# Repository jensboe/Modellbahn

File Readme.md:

# System architecture
The `adapter board A` is connected to a nucleo 64 board.
The `adapter board A` provides a 
```mermaid
block-beta

columns 1
block:selfmade
    block:base
        columns 1
        nucleo
        adapter["adapter board A"]
    end
    space
    expansion_1["expansion board A 1"]
    space
    expansion_n["expansion board A n"]
    space
    expansion_b["expansion board B"]
    adapter     <--> expansion_1
    expansion_1   ----> expansion_n
    expansion_n  ----> expansion_b
    style expansion_b stroke:#333,stroke-dasharray: 5 5;
end
space
block:extern
    power_supply
    track_1
    switch_1_a
    switch_1_b
    track_x
    switch_y_a
    switch_y_b
end
power_supply --> adapter
expansion_1 --> track_1
expansion_1 --> switch_1_a
expansion_1 --> switch_1_b

expansion_n --> track_x
expansion_n --> switch_y_a
expansion_n --> switch_y_b
```
## Connection between expansion boards
Required Wires:
1. Drive Ground
2. Drive voltage
3. Switch voltage
4. Vcc (3V3 or 5V?)
5. D_Ground
6. MOSI
7. MISO
8. CLK

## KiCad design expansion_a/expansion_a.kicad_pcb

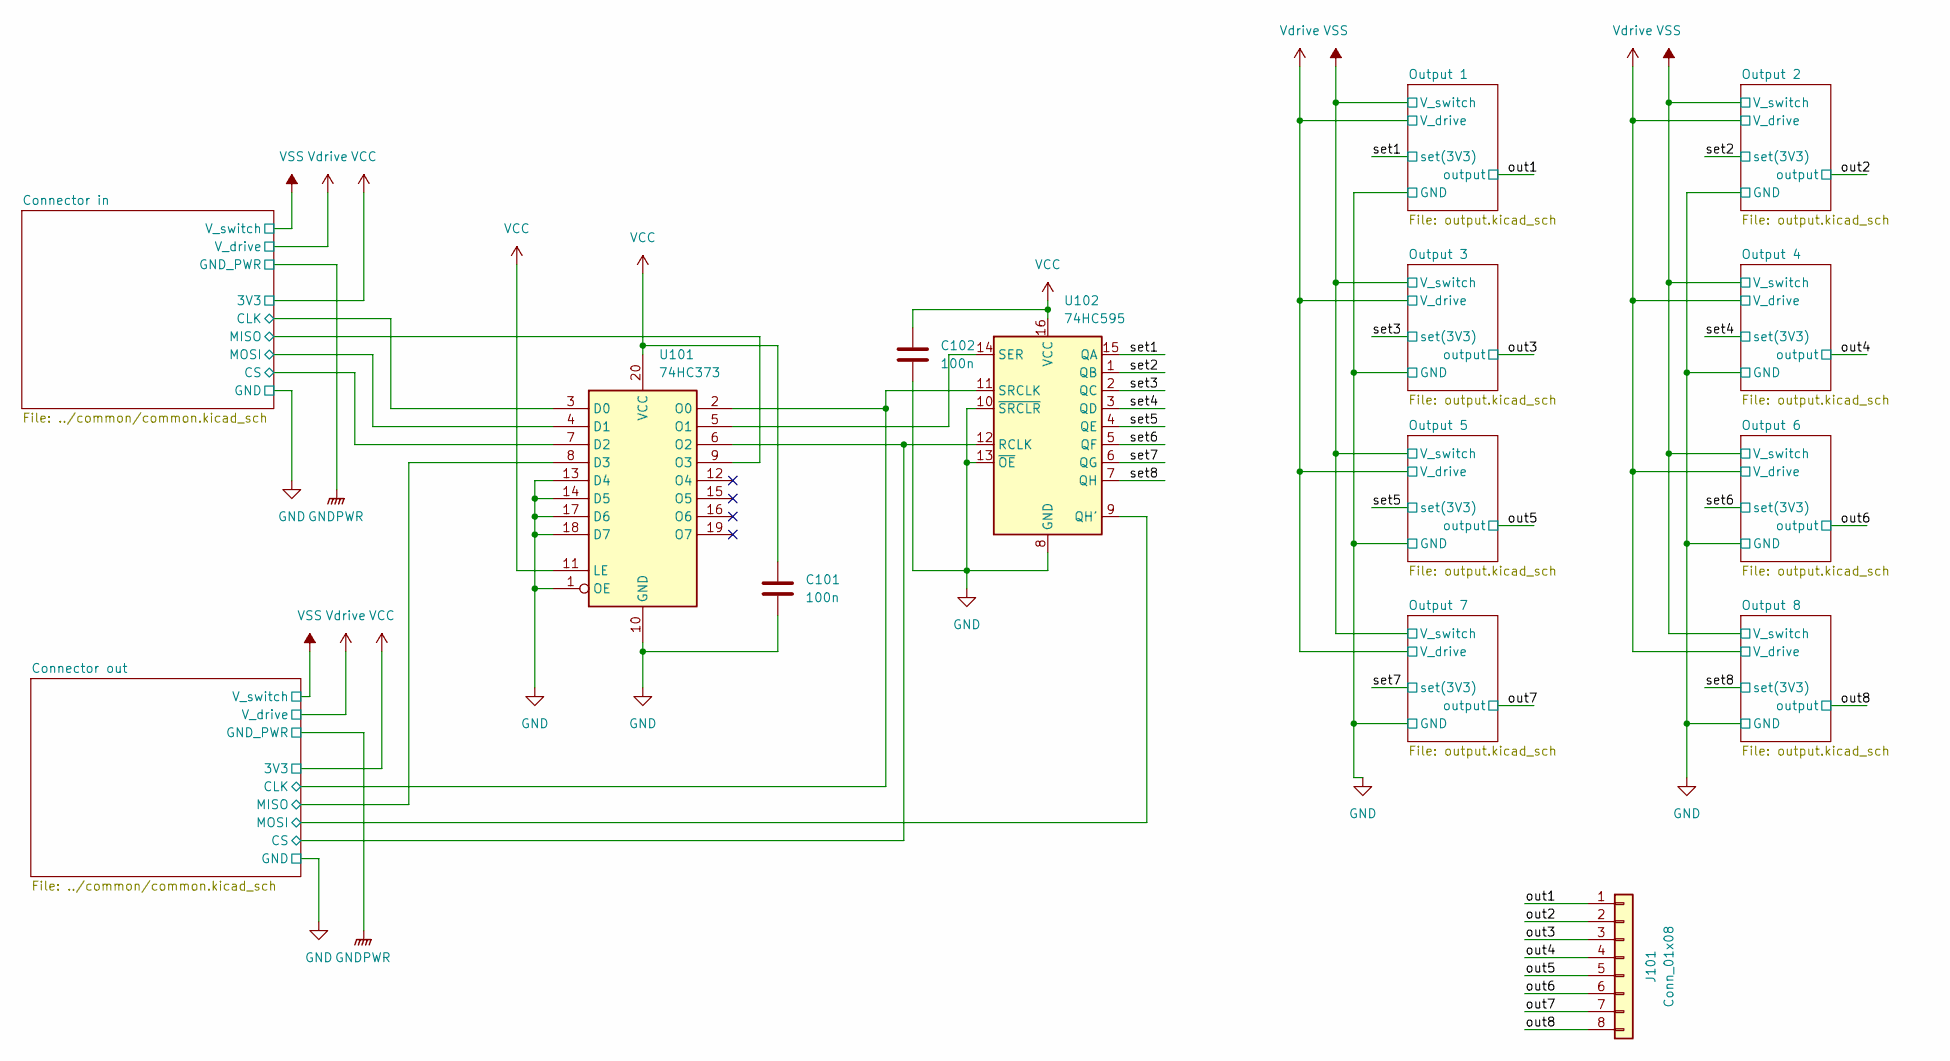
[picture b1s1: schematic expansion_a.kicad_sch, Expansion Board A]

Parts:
C101, C102: 100n; C_0805_2012Metric; LCSC C28233
J101: Conn_01x08; TerminalBlock_4Ucon_1x08_P3.50mm_Vertical; LCSC C976562
U101: 74HC373; SO-20_5.3x12.6mm_P1.27mm; LCSC C22374060
U102: 74HC595; SOIC-16W_5.3x10.2mm_P1.27mm; LCSC C5947

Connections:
/Connector in/CLK: U101.3 (D0); also elsewhere on the board
/Connector in/CS: U101.7 (D2); also elsewhere on the board
/Connector in/MISO: U101.9 (O3); also elsewhere on the board
/Connector in/MOSI: U101.4 (D1); also elsewhere on the board
/Connector out/CLK: U101.2 (O0), U102.11 (SRCLK); also elsewhere on the board
/Connector out/CS: U101.6 (O2), U102.12 (RCLK); also elsewhere on the board
/Connector out/MISO: U101.8 (D3); also elsewhere on the board
/Connector out/MOSI: U102.9 (QH'); also elsewhere on the board
/out1: J101.1; also elsewhere on the board
/out2: J101.2; also elsewhere on the board
/out3: J101.3; also elsewhere on the board
/out4: J101.4; also elsewhere on the board
/out5: J101.5; also elsewhere on the board
/out6: J101.6; also elsewhere on the board
/out7: J101.7; also elsewhere on the board
/out8: J101.8; also elsewhere on the board
/set1: U102.15 (QA); also elsewhere on the board
/set2: U102.1 (QB); also elsewhere on the board
/set3: U102.2 (QC); also elsewhere on the board
/set4: U102.3 (QD); also elsewhere on the board
/set5: U102.4 (QE); also elsewhere on the board
/set6: U102.5 (QF); also elsewhere on the board
/set7: U102.6 (QG); also elsewhere on the board
/set8: U102.7 (QH); also elsewhere on the board
GND: C101.2, C102.2, U101.1 (OE), U101.10 (GND), U101.13 (D4), U101.14 (D5), U101.17 (D6), U101.18 (D7), U102.8 (GND), U102.10 (~SRCLR), U102.13 (~OE); also elsewhere on the board
unnamed: U101.5 (O1), U102.14 (SER)
VCC: C101.1, C102.1, U101.11 (LE), U101.20 (VCC), U102.16 (VCC); also elsewhere on the board

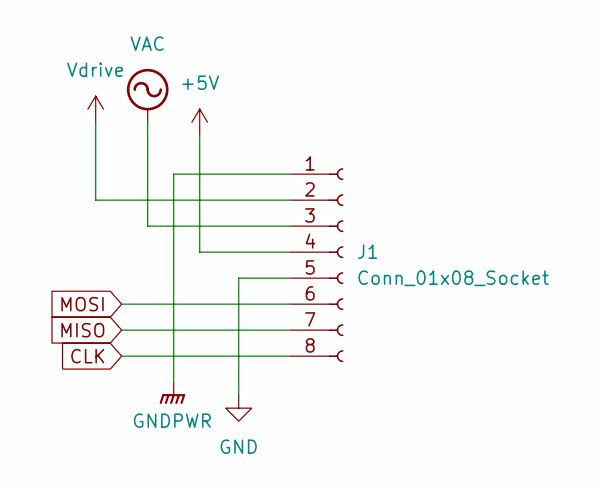
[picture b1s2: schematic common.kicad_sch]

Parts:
J1: Conn_01x08_Socket; TerminalBlock_4Ucon_1x08_P3.50mm_Vertical; LCSC C976562

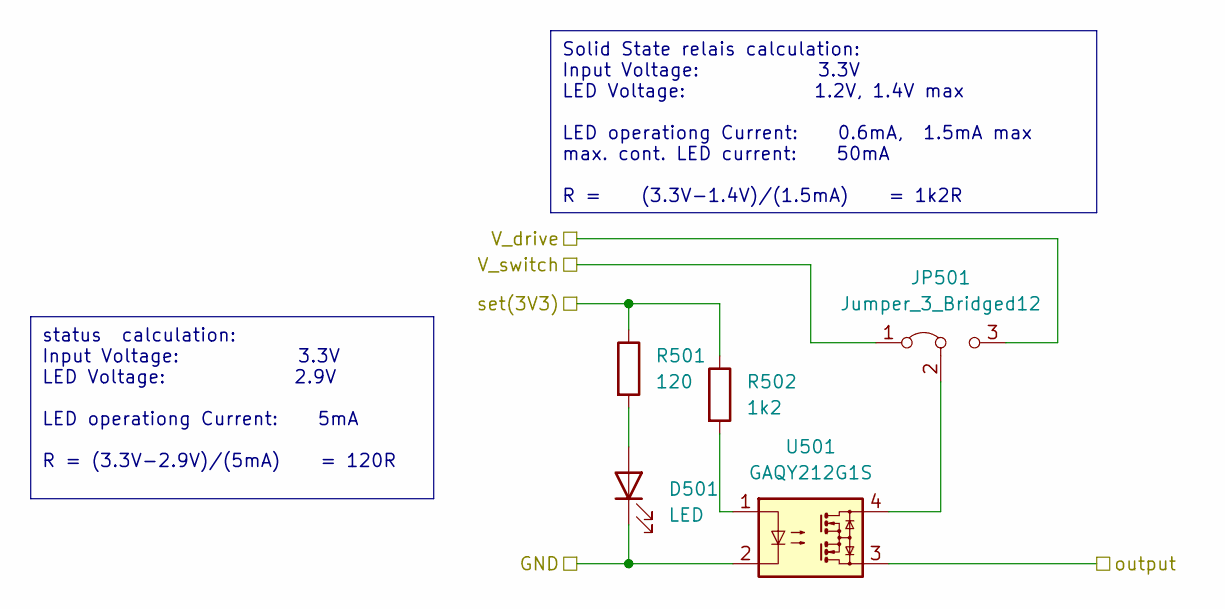
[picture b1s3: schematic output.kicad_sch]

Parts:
D501: LED; CP_EIA-3528-12_Kemet-T; LCSC C2290
JP501: Jumper_3_Bridged12; PinHeader_1x03_P2.54mm_Vertical; LCSC C124376
R501: 120; R_0805_2012Metric; LCSC C17437
R502: 1k2; R_0805_2012Metric; LCSC C17379
U501: GAQY212G1S; SO-4_4.4x3.9mm_P2.54mm; LCSC C7435108

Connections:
/out3: U501.3; also elsewhere on the board
/set3: R501.1, R502.1; also elsewhere on the board
GND: D501.1 (K), U501.2; also elsewhere on the board
unnamed: D501.2 (A), R501.2
unnamed: JP501.2 (C), U501.4
unnamed: R502.2, U501.1
VSS: JP501.1 (A); also elsewhere on the board
Vdrive: JP501.3 (B); also elsewhere on the board

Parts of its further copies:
D301, D401, D601, D701, D801, D901, D1001: LED; CP_EIA-3528-12_Kemet-T; LCSC C2290
JP301, JP401, JP601, JP701, JP801, JP901, JP1001: Jumper_3_Bridged12; PinHeader_1x03_P2.54mm_Vertical; LCSC C124376
R301, R401, R601, R701, R801, R901, R1001: 120; R_0805_2012Metric; LCSC C17437
R302, R402, R602, R702, R802, R902, R1002: 1k2; R_0805_2012Metric; LCSC C17379
U301, U401, U601, U701, U801, U901, U1001: GAQY212G1S; SO-4_4.4x3.9mm_P2.54mm; LCSC C7435108

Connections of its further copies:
/out1: U301.3; also elsewhere on the board
/out2: U401.3; also elsewhere on the board
/out4: U601.3; also elsewhere on the board
/out5: U701.3; also elsewhere on the board
/out6: U801.3; also elsewhere on the board
/out7: U901.3; also elsewhere on the board
/out8: U1001.3; also elsewhere on the board
/set1: R301.1, R302.1; also elsewhere on the board
/set2: R401.1, R402.1; also elsewhere on the board
/set4: R601.1, R602.1; also elsewhere on the board
/set5: R701.1, R702.1; also elsewhere on the board
/set6: R801.1, R802.1; also elsewhere on the board
/set7: R901.1, R902.1; also elsewhere on the board
/set8: R1001.1, R1002.1; also elsewhere on the board
GND: D301.1 (K), D401.1 (K), D601.1 (K), D701.1 (K), D801.1 (K), D901.1 (K), D1001.1 (K), U301.2, U401.2, U601.2, U701.2, U801.2, U901.2, U1001.2; also elsewhere on the board
unnamed: D301.2 (A), R301.2
unnamed: D401.2 (A), R401.2
unnamed: D601.2 (A), R601.2
unnamed: D701.2 (A), R701.2
unnamed: D801.2 (A), R801.2
unnamed: D901.2 (A), R901.2
unnamed: D1001.2 (A), R1001.2
unnamed: JP301.2 (C), U301.4
unnamed: JP401.2 (C), U401.4
unnamed: JP601.2 (C), U601.4
unnamed: JP701.2 (C), U701.4
unnamed: JP801.2 (C), U801.4
unnamed: JP901.2 (C), U901.4
unnamed: JP1001.2 (C), U1001.4
unnamed: R302.2, U301.1
unnamed: R402.2, U401.1
unnamed: R602.2, U601.1
unnamed: R702.2, U701.1
unnamed: R802.2, U801.1
unnamed: R902.2, U901.1
unnamed: R1002.2, U1001.1
VSS: JP301.1 (A), JP401.1 (A), JP601.1 (A), JP701.1 (A), JP801.1 (A), JP901.1 (A), JP1001.1 (A); also elsewhere on the board
Vdrive: JP301.3 (B), JP401.3 (B), JP601.3 (B), JP701.3 (B), JP801.3 (B), JP901.3 (B), JP1001.3 (B); also elsewhere on the board

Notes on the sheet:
Solid State relais calculation: Input Voltage: 3.3V LED Voltage: 1.2V, 1.4V max LED operationg Current: 0.6mA, 1.5mA max max. cont. LED current: 50mA R = (3.3V-1.4V)/(1.5mA) = 1k2R
status calculation: Input Voltage: 3.3V LED Voltage: 2.9V LED operationg Current: 5mA R = (3.3V-2.9V)/(5mA) = 120R

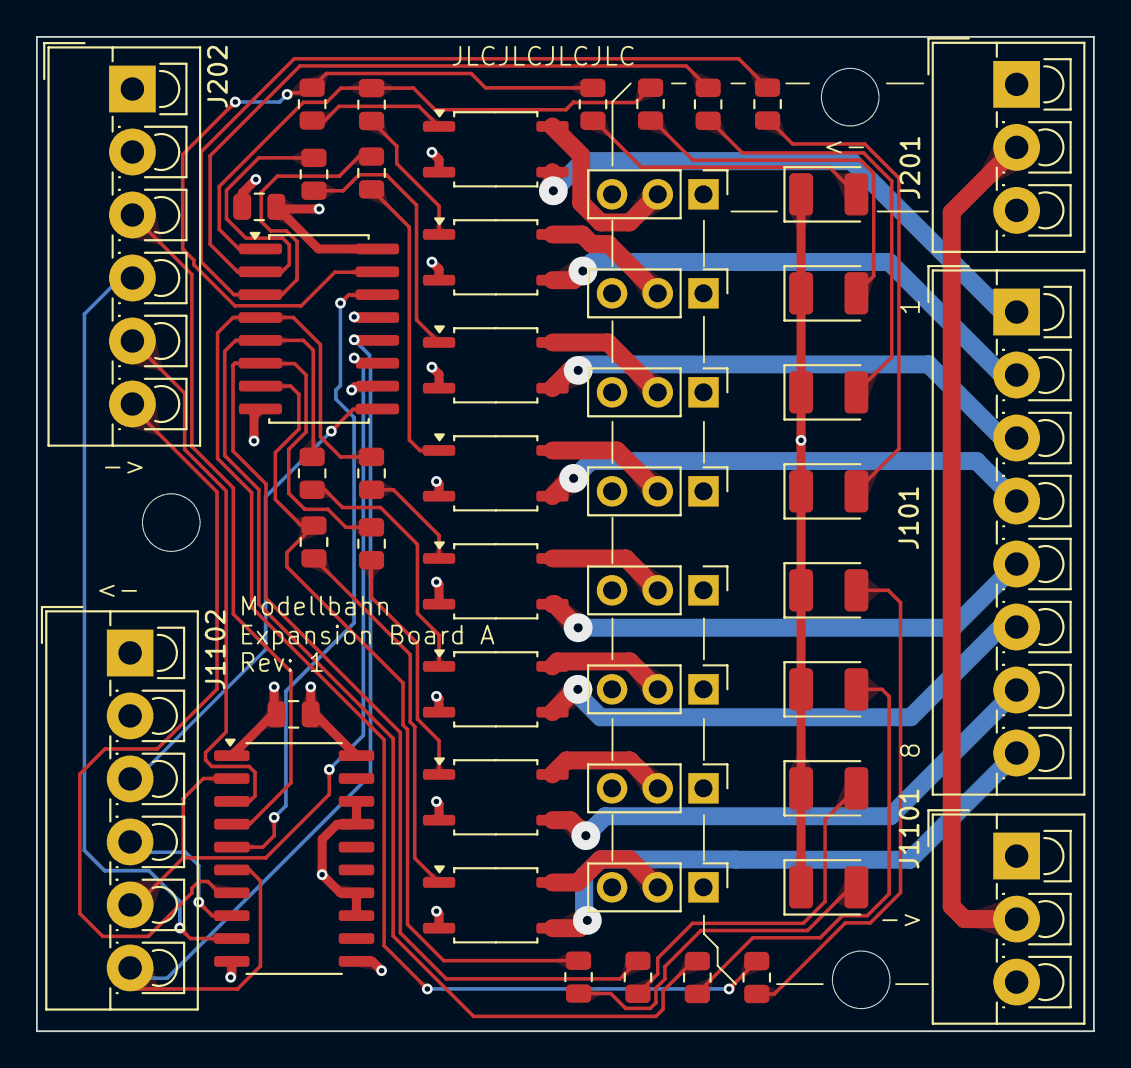
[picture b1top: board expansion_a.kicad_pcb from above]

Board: 4 copper layers, 58.7 x 55.2 mm, 52 parts (0 on the bottom side), 54 nets.

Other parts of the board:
J201, J1101: Conn_01x03; TerminalBlock_4Ucon_1x03_P3.50mm_Vertical
J202, J1102: Conn_01x06; TerminalBlock_4Ucon_1x06_P3.50mm_Vertical
REF1, REF2, REF3: MountingHole_3.2mm_M3

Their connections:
/Connector in/CLK: J202.5; also elsewhere on the board
/Connector in/CS: J202.6; also elsewhere on the board
/Connector in/MISO: J202.4; also elsewhere on the board
/Connector in/MOSI: J202.3; also elsewhere on the board
/Connector out/CLK: J1102.5; also elsewhere on the board
/Connector out/CS: J1102.6; also elsewhere on the board
/Connector out/MISO: J1102.4; also elsewhere on the board
/Connector out/MOSI: J1102.3; also elsewhere on the board
GND: J202.2, J1102.2; also elsewhere on the board
GNDPWR: J201.2, J1101.2
VCC: J202.1, J1102.1; also elsewhere on the board
VSS: J201.3, J1101.3; also elsewhere on the board
Vdrive: J201.1, J1101.1; also elsewhere on the board

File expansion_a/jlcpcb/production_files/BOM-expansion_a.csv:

Comment,Designator,Footprint,LCSC,Quantity
Jumper_3_Bridged12,"JP1001,JP301,JP401,JP501,JP601,JP701,JP801,JP901",PinHeader_1x03_P2.54mm_Vertical,C124376,8
1k2,"R1002,R302,R402,R502,R602,R702,R802,R902",R_0805_2012Metric,C17379,8
120,"R1001,R301,R401,R501,R601,R701,R801,R901",R_0805_2012Metric,C17437,8
74HC373,U101,SO-20_5.3x12.6mm_P1.27mm,C22374060,1
100n,"C101,C102",C_0805_2012Metric,C28233,2
LED,"D1001,D301,D401,D501,D601,D701,D801,D901",CP_EIA-3528-12_Kemet-T,C5246350,8
74HC595,U102,SOIC-16W_5.3x10.2mm_P1.27mm,C5947,1
GAQY212G1S,"U1001,U301,U401,U501,U601,U701,U801,U901",SO-4_4.4x3.9mm_P2.54mm,C7435108,8
Conn_01x03,"J1101,J201",TerminalBlock_4Ucon_1x03_P3.50mm_Vertical,C976557,2
Conn_01x06,"J1102,J202",TerminalBlock_4Ucon_1x06_P3.50mm_Vertical,C976560,2
Conn_01x08,J101,TerminalBlock_4Ucon_1x08_P3.50mm_Vertical,C976562,1

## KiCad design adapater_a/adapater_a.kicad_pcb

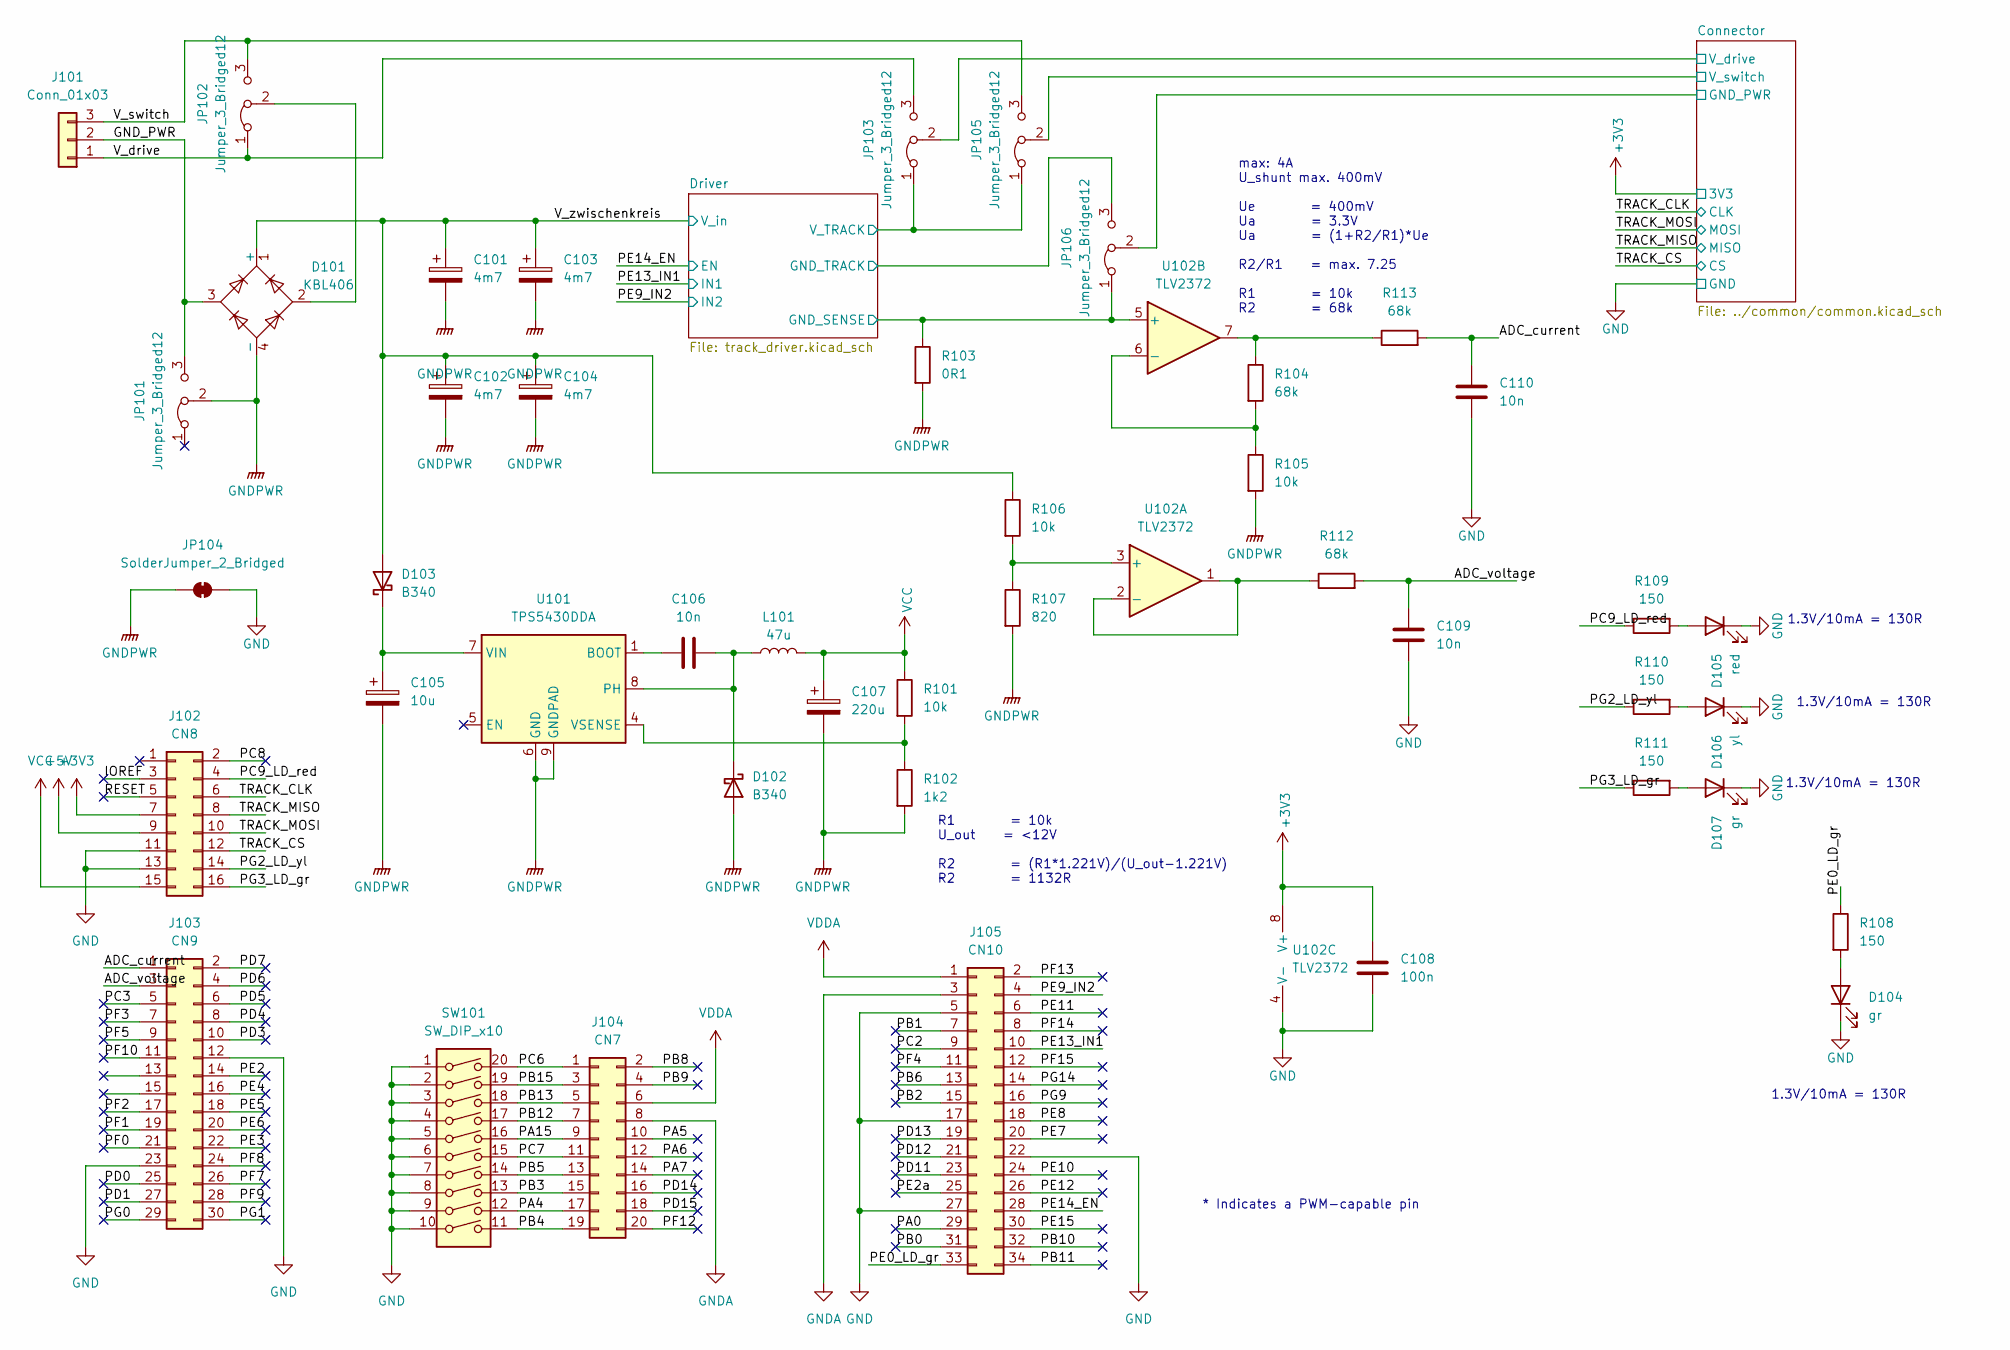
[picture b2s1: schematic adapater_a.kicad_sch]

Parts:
C101, C102, C103, C104: 4m7; CP_Radial_D18.0mm_P7.50mm; LCSC C92163
C105: 10u; CP_Elec_6.3x5.4; LCSC C29199
C106, C109, C110: 10n; C_0805_2012Metric; LCSC C1710
C107: 220u; C_Elec_10x10.2; LCSC C3358
C108: 100n; C_0805_2012Metric; LCSC C28233
D101: KBL406; Diode_Bridge_Vishay_KBL; LCSC C3078
D102, D103: B340; D_SMA; LCSC C64982
D104, D107: gr; LED_0805_2012Metric; LCSC C2297
D105: red; LED_0805_2012Metric; LCSC C84256
D106: yl; LED_0805_2012Metric; LCSC C2296
J101: Conn_01x03; TerminalBlock_4Ucon_1x03_P3.50mm_Vertical; LCSC C976557
J102: CN8; PinHeader_2x08_P2.54mm_Vertical; LCSC C68234
J103: CN9; PinHeader_2x15_P2.54mm_Vertical; LCSC C56496
J104: CN7; PinHeader_2x10_P2.54mm_Vertical; LCSC C5116480
J105: CN10; PinHeader_2x17_P2.54mm_Vertical; LCSC C2685134
JP101, JP102, JP103, JP105, JP106: Jumper_3_Bridged12; PinHeader_1x03_P2.54mm_Vertical; LCSC C124376
JP104: SolderJumper_2_Bridged; SolderJumper-2_P1.3mm_Bridged_RoundedPad1.0x1.5mm
L101: 47u; L_Ferrocore_DLG-0504; LCSC C9889
R101, R105, R106: 10k; R_0805_2012Metric; LCSC C17414
R102: 1k2; R_0805_2012Metric; LCSC C17379
R103: 0R1; R_1206_3216Metric; LCSC C25334
R104, R112, R113: 68k; R_0805_2012Metric; LCSC C17801
R107: 820; R_0805_2012Metric; LCSC C23253
R108, R109, R110, R111: 150; R_0805_2012Metric; LCSC C17471
SW101: SW_DIP_x10; SW_DIP_SPSTx10_Slide_KingTek_DSHP10TS_W7.62mm_P1.27mm; LCSC C314500
U101: TPS5430DDA; TI_SO-PowerPAD-8_ThermalVias; LCSC C9864
U102: TLV2372; SOIC-8_3.9x4.9mm_P1.27mm; LCSC C27204

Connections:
+3V3: C108.1, J102.7, U102.8 (V+); also elsewhere on the board
+5V: J102.9
/ADC_current: C110.2, J103.1, R113.2
/ADC_voltage: C109.2, J103.3, R112.2
/Connector/GND_PWR: JP106.2 (C); also elsewhere on the board
/Connector/V_drive: JP103.2 (C); also elsewhere on the board
/Connector/V_switch: JP105.2 (C); also elsewhere on the board
/Driver/GND_SENSE: JP106.1 (A), R103.1, U102.5 (+); also elsewhere on the board
/Driver/GND_TRACK: JP106.3 (B); also elsewhere on the board
/Driver/V_TRACK: JP103.1 (A), JP105.1 (A); also elsewhere on the board
/GND_PWR: D101.3, J101.2, JP101.3 (B)
/IOREF: J102.3
/PA0: J105.29
/PA4: J104.17, SW101.12
/PA5: J104.10
/PA6: J104.12
/PA7: J104.14
/PA15: J104.9, SW101.16
/PB0: J105.31
/PB1: J105.7
/PB2: J105.15
/PB3: J104.15, SW101.13
/PB4: J104.19, SW101.11
/PB5: J104.13, SW101.14
/PB6: J105.13
/PB8: J104.2
/PB9: J104.4
/PB10: J105.32
/PB11: J105.34
/PB12: J104.7, SW101.17
/PB13: J104.5, SW101.18
/PB15: J104.3, SW101.19
/PC2: J105.9
/PC3: J103.5
/PC6: J104.1, SW101.20
/PC7: J104.11, SW101.15
/PC8: J102.2
/PC9_LD_red: J102.4, R109.1
/PD0: J103.25
/PD1: J103.27
/PD3: J103.10
/PD4: J103.8
/PD5: J103.6
/PD6: J103.4
/PD7: J103.2
/PD11: J105.23
/PD12: J105.21
/PD13: J105.19
/PD14: J104.16
/PD15: J104.18
/PE0_LD_gr: J105.33, R108.1
/PE2: J103.14
/PE2a: J105.25
/PE3: J103.22
/PE4: J103.16
/PE5: J103.18
/PE6: J103.20
/PE7: J105.20
/PE8: J105.18
/PE9_IN2: J105.4; also elsewhere on the board
/PE10: J105.24
/PE11: J105.6
/PE12: J105.26
/PE13_IN1: J105.10; also elsewhere on the board
/PE14_EN: J105.28; also elsewhere on the board
/PE15: J105.30
/PF0: J103.21
/PF1: J103.19
/PF2: J103.17
/PF3: J103.7
/PF4: J105.11
/PF5: J103.9
/PF7: J103.26
/PF8: J103.24
/PF9: J103.28
/PF10: J103.11
/PF12: J104.20
/PF13: J105.2
/PF14: J105.8
/PF15: J105.12
/PG0: J103.29
/PG1: J103.30
/PG2_LD_yl: J102.14, R110.1
/PG3_LD_gr: J102.16, R111.1
/PG9: J105.16
/PG14: J105.14
/RESET: J102.5
/TRACK_CLK: J102.6; also elsewhere on the board
/TRACK_CS: J102.12; also elsewhere on the board
/TRACK_MISO: J102.8; also elsewhere on the board
/TRACK_MOSI: J102.10; also elsewhere on the board
/V_drive: J101.1, JP102.1 (A), JP103.3 (B)
/V_switch: J101.3, JP102.3 (B), JP105.3 (B)
/V_zwischenkreis: C101.1, C102.1, C103.1, C104.1, D101.1 (+), D103.2 (A), R106.1; also elsewhere on the board
GND: C108.2, C109.1, C110.1, D104.1 (K), D105.1 (K), D106.1 (K), D107.1 (K), J102.11, J102.13, J103.12, J103.23, J105.5, J105.17, J105.22, J105.27, JP104.2 (B), SW101.1, SW101.2, SW101.3, SW101.4, SW101.5, SW101.6, SW101.7, SW101.8, SW101.9, SW101.10, U102.4 (V-); also elsewhere on the board
GNDA: J104.8, J105.3
GNDPWR: C101.2, C102.2, C103.2, C104.2, C105.2, C107.2, D101.4 (-), D102.2 (A), JP101.2 (C), JP104.1 (A), R102.2, R103.2, R105.2, R107.2, U101.6 (GND), U101.9 (GNDPAD); also elsewhere on the board
unnamed: C106.2, D102.1 (K), L101.1, U101.8 (PH)
unnamed: C105.1, D103.1 (K), U101.7 (VIN)
unnamed: D104.2 (A), R108.2
unnamed: D105.2 (A), R109.2
unnamed: D106.2 (A), R110.2
unnamed: D107.2 (A), R111.2
unnamed: D101.2, JP102.2 (C)
unnamed: R104.1, R113.1, U102.7
unnamed: C106.1, U101.1 (BOOT)
unnamed: R101.2, R102.1, U101.4 (VSENSE)
unnamed: R106.2, R107.1, U102.3 (+)
unnamed: R112.1, U102.1, U102.2 (-)
unnamed: R104.2, R105.1, U102.6 (-)
VCC: C107.1, J102.15, L101.2, R101.1
VDDA: J104.6, J105.1

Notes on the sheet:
1.3V/10mA = 130R
R1 = 10k U_out = <12V R2 = (R1*1.221V)/(U_out-1.221V) R2 = 1132R
max: 4A U_shunt max. 400mV Ue = 400mV Ua = 3.3V Ua = (1+R2/R1)*Ue R2/R1 = max. 7.25 R1 = 10k R2 = 68k
* Indicates a PWM-capable pin

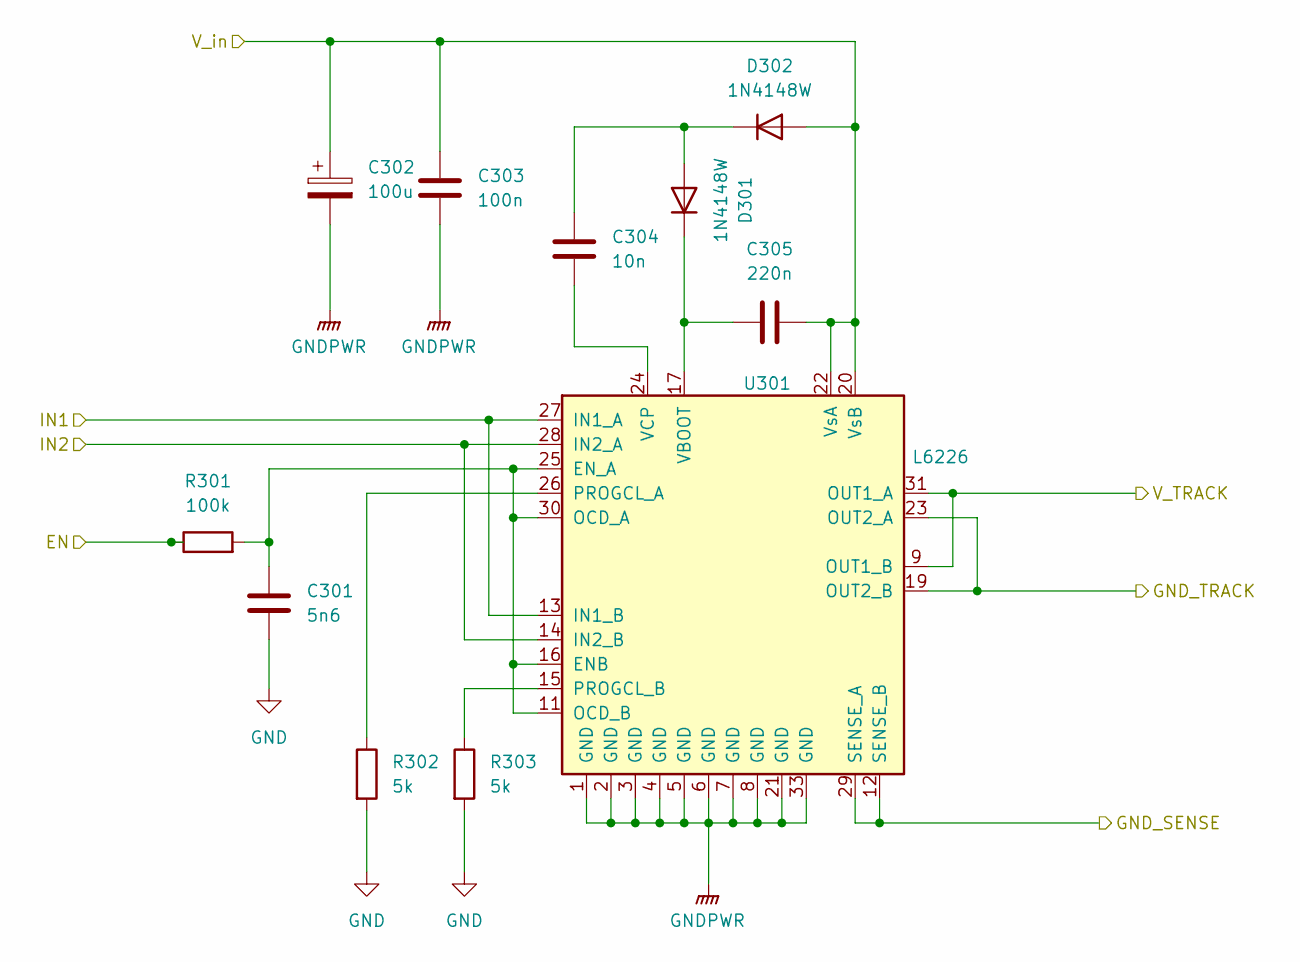
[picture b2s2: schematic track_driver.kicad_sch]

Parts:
C301: 5n6; C_0805_2012Metric; LCSC C56078
C302: 100u; CP_Elec_6.3x5.4; LCSC C37308
C303: 100n; C_0805_2012Metric; LCSC C28233
C304: 10n; C_0805_2012Metric; LCSC C1710
C305: 220n; C_0805_2012Metric; LCSC C1710
D301, D302: 1N4148W; D_SOD-123; LCSC C81598
R301: 100k; R_0805_2012Metric; LCSC C149504
R302, R303: 5k; R_0805_2012Metric; LCSC C17379
U301: L6226; UFQFPN-32-1EP_5x5mm_P0.5mm_EP3.5x3.5mm; LCSC C95357

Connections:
/Driver/GND_SENSE: U301.12 (SENSE_B), U301.29 (SENSE_A); also elsewhere on the board
/Driver/GND_TRACK: U301.19 (OUT2_B), U301.23 (OUT2_A); also elsewhere on the board
/Driver/V_TRACK: U301.9 (OUT1_B), U301.31 (OUT1_A); also elsewhere on the board
/PE9_IN2: U301.14 (IN2_B), U301.28 (IN2_A); also elsewhere on the board
/PE13_IN1: U301.13 (IN1_B), U301.27 (IN1_A); also elsewhere on the board
/PE14_EN: R301.1; also elsewhere on the board
/V_zwischenkreis: C302.1, C303.1, C305.2, D302.2 (A), U301.20 (VsB), U301.22 (VsA); also elsewhere on the board
GND: C301.2, R302.2, R303.2; also elsewhere on the board
GNDPWR: C302.2, C303.2, U301.1 (GND), U301.2 (GND), U301.3 (GND), U301.4 (GND), U301.5 (GND), U301.6 (GND), U301.7 (GND), U301.8 (GND), U301.21 (GND), U301.33 (GND); also elsewhere on the board
unnamed: C304.1, D301.2 (A), D302.1 (K)
unnamed: C305.1, D301.1 (K), U301.17 (VBOOT)
unnamed: C301.1, R301.2, U301.11 (OCD_B), U301.16 (ENB), U301.25 (EN_A), U301.30 (OCD_A)
unnamed: R302.1, U301.26 (PROGCL_A)
unnamed: R303.1, U301.15 (PROGCL_B)
unnamed: C304.2, U301.24 (VCP)

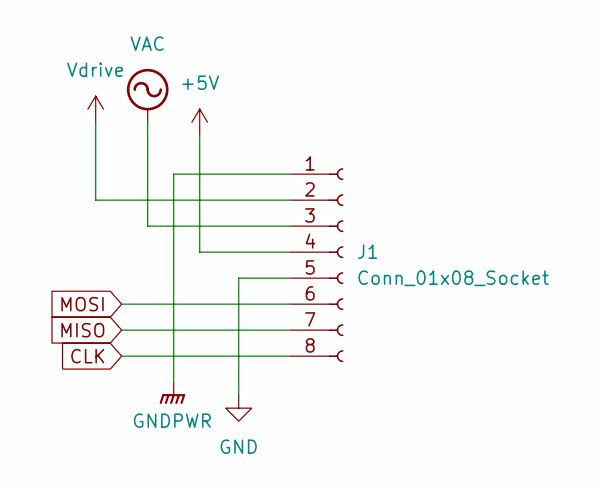
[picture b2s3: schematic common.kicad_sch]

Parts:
J1: Conn_01x08_Socket; TerminalBlock_4Ucon_1x08_P3.50mm_Vertical; LCSC C976562

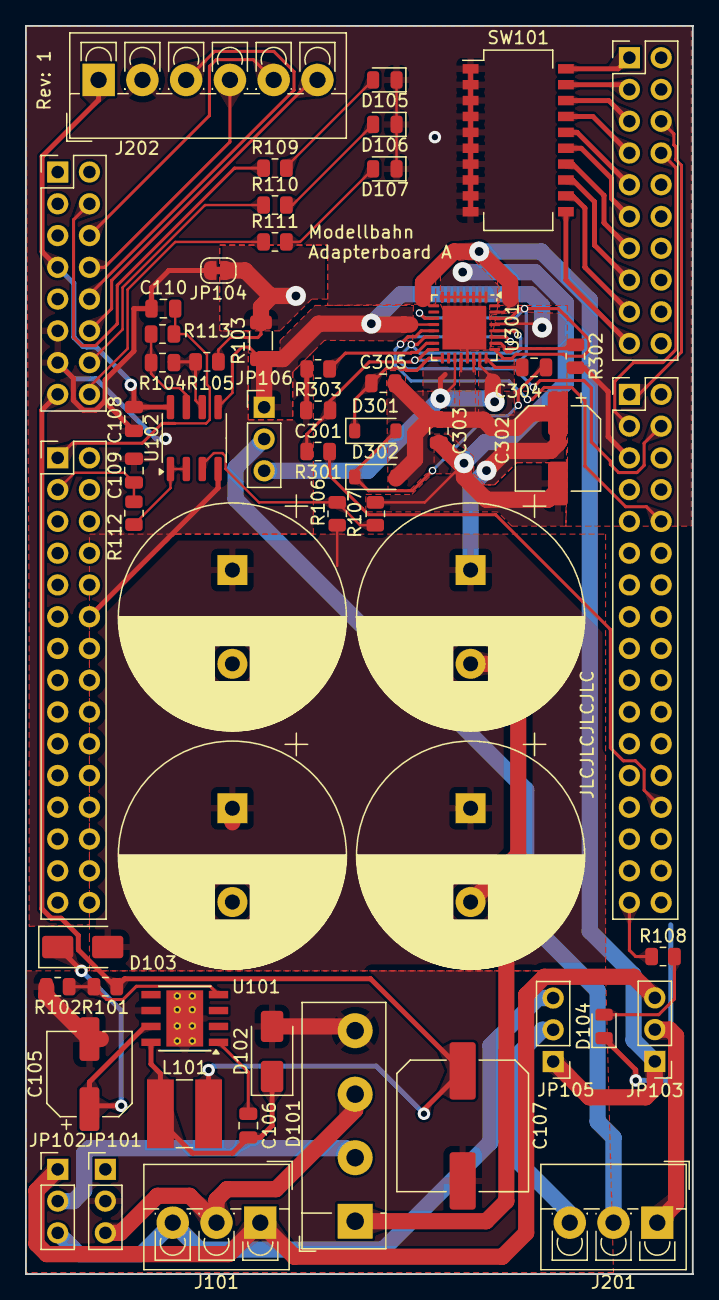
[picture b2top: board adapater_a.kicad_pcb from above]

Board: 2 copper layers, 53.3 x 99.8 mm, 58 parts (0 on the bottom side), 58 nets.

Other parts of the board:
J201: Conn_01x03; TerminalBlock_4Ucon_1x03_P3.50mm_Vertical
J202: Conn_01x06; TerminalBlock_4Ucon_1x06_P3.50mm_Vertical

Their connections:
+3V3: J202.1; also elsewhere on the board
/Connector/GND_PWR: J201.2; also elsewhere on the board
/Connector/V_drive: J201.1; also elsewhere on the board
/Connector/V_switch: J201.3; also elsewhere on the board
/TRACK_CLK: J202.5; also elsewhere on the board
/TRACK_CS: J202.6; also elsewhere on the board
/TRACK_MISO: J202.4; also elsewhere on the board
/TRACK_MOSI: J202.3; also elsewhere on the board
GND: J202.2; also elsewhere on the board

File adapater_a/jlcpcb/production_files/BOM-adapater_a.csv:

Comment,Designator,Footprint,LCSC,Quantity
CN7,J104,PinHeader_2x10_P2.54mm_Vertical,C124359,1
Jumper_3_Bridged12,"JP101,JP102,JP103,JP105,JP106",PinHeader_1x03_P2.54mm_Vertical,C124376,5
100k,R301,R_0805_2012Metric,C149504,1
10n,"C106,C304,C305",C_0805_2012Metric,C1710,3
1k2,"R102,R302,R303",R_0805_2012Metric,C17379,3
10k,"R101,R105",R_0805_2012Metric,C17414,2
68k,R104,R_0805_2012Metric,C17801,1
0R1,R103,R_1206_3216Metric,C25334,1
CN10,J105,PinHeader_2x17_P2.54mm_Vertical,C2685134,1
TLV2372,U102,SOIC-8_3.9x4.9mm_P1.27mm,C27204,1
100n,"C108,C303",C_0805_2012Metric,C28233,2
10u,C105,CP_Elec_6.3x5.4,C29199,1
KBL406,D101,Diode_Bridge_Vishay_KBL,C3078,1
220u,C107,C_Elec_10x10.2,C3358,1
100u,C302,CP_Elec_6.3x5.4,C37308,1
5n6,C301,C_0805_2012Metric,C56078,1
CN9,J103,PinHeader_2x15_P2.54mm_Vertical,C56496,1
B340,D102,D_SMA,C64982,1
CN8,J102,PinHeader_2x08_P2.54mm_Vertical,C68234,1
1N4148W,"D301,D302",D_SOD-123,C81598,2
4m7,"C101,C102,C103,C104",CP_Radial_D18.0mm_P7.50mm,C92163,4
L6226,U301,UFQFPN-32-1EP_5x5mm_P0.5mm_EP3.5x3.5mm,C95357,1
Conn_01x03,"J101,J201",TerminalBlock_4Ucon_1x03_P3.50mm_Vertical,C976557,2
Conn_01x06,J202,TerminalBlock_4Ucon_1x06_P3.50mm_Vertical,C976560,1
TPS5430DDA,U101,TI_SO-PowerPAD-8_ThermalVias,C9864,1
47u,L101,L_Ferrocore_DLG-0504,C9889,1

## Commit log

2024-12-31 Add git ignore
2024-12-31 Add project
2024-12-31 Add nucleo expander board and schematic
2024-12-31 Set doc properties, ignore backups
2024-12-31 Add readme with system overview
2024-12-31 Improve git ignore
2024-12-31 Remove main project
2024-12-31 Add project for expansion board
2024-12-31 Add common project for chared ressources
2024-12-31 Add project for adapter a
2024-12-31 Add common connector
2024-12-31 Ignore old schematics
2024-12-31 expansion schematics added
2024-12-31 Error free expansion board
2024-12-31 expansion schematic error free
2025-01-01 Finalise expansion A.
2025-01-01 Expander Final II
2025-01-01 Add JLCPC Tools production data output
2025-01-01 Remove right angle in GND wire.
2025-01-01 Rotate parts according to JLC §D view
2025-01-01 Rename common "+5V" to "3V3"
2025-01-02 Add capacitors for ic
2025-01-02 Silk screen improvments
2025-01-02 Add first version of adpater A
2025-01-02 Realgin nucleo connection
2025-01-02 Add voltage messurement
2025-01-04 Update adapter A
2025-01-04 Add missing trace for zwischenkreis
2025-01-04 Nicer signal names
2025-01-04 adapter A: Generate production files
2025-01-04 State of production
2025-01-04 Update Expansion board A
